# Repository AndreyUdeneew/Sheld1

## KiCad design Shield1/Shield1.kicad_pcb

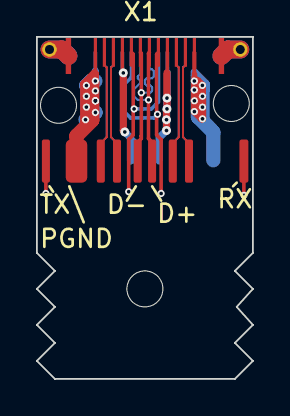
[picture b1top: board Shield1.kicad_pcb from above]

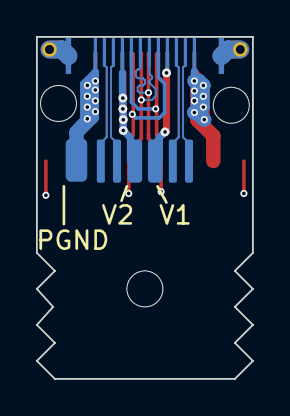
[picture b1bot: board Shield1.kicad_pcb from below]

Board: 4 copper layers, 12.0 x 19.0 mm, 17 parts (6 on the bottom side), 17 nets.

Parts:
J1, J2, J5, J6, J7, J8, J9, J10, J11, J12, J13, J14: Conn_01x01_Male; smdPin
J3, J15, J17, J25: Conn_01x01_Male; throughPin
X1: USB_C_24pins; FPC_12

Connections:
D+: J6.1, X1.A6 (D+), X1.B6 (D+)
D-: J5.1, X1.A7 (D-), X1.B7 (D-)
Earth: J17.1, J25.1, X1.S1 (SHIELD)
GND: X1.A12 (GND), X1.B1 (GND)
GND3: X1.A1 (GND), X1.B12 (GND)
RX: J3.1, X1.A5 (CC1), X1.B5 (CC2)
RX1+: J8.1, X1.B11 (RX1+)
RX1-: J7.1, X1.B10 (RX1-)
RX2+: J12.1, X1.A11 (RX2+)
RX2-: J11.1, X1.A10 (RX2-)
TX: J15.1, X1.A8 (SBU1), X1.B8 (SBU2)
TX1+: J10.1, X1.A2 (TX1+)
TX1-: J9.1, X1.A3 (TX1-)
TX2+: J14.1, X1.B2 (TX2+)
TX2-: J13.1, X1.B3 (TX2-)
VBUS1: J1.1, X1.A4 (VBUS), X1.B9 (VBUS)
VBUS2: J2.1, X1.A9 (VBUS), X1.B4 (VBUS)

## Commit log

2022-10-10 v0.1 circuit prototype
2022-10-10 v0.2 circuit is ready
2022-10-10 v0.3 Cшксгше was reduced, initial decpmposition has been completed
2022-10-10 v0.4 design rules have been added
2022-10-13 v0.5 Decomposition has been completed, form has been created
2022-10-13 v0.6 actual state
2022-10-13 v0.61 actual state
2022-10-16 v0.7 Circuit has been corrected
2022-10-17 v0.8 some nets have been routed
2022-10-17 Auto stash before merge of "main" and "origin/main"
2022-10-17 v0.9 Some more nets have been routed
2022-10-17 v0.91 some changes
2022-10-18 v0.92 all the nets have been routed
2022-10-18 v0.93 correct file has been restored
2022-10-18 v0.94 cir-pcb connection has been restored
2022-10-18 v0.95 need 4 checkup
2022-10-18 v0.96 Rx, Tx were hidden and moved
2022-10-21 v0.97 Seems 2B ready
2022-10-21 v0.98 Gerbers have been created
2022-12-14 v0.99 GND has been corrected
2023-07-25 v1.0 Penny 3 to Rezonit!
